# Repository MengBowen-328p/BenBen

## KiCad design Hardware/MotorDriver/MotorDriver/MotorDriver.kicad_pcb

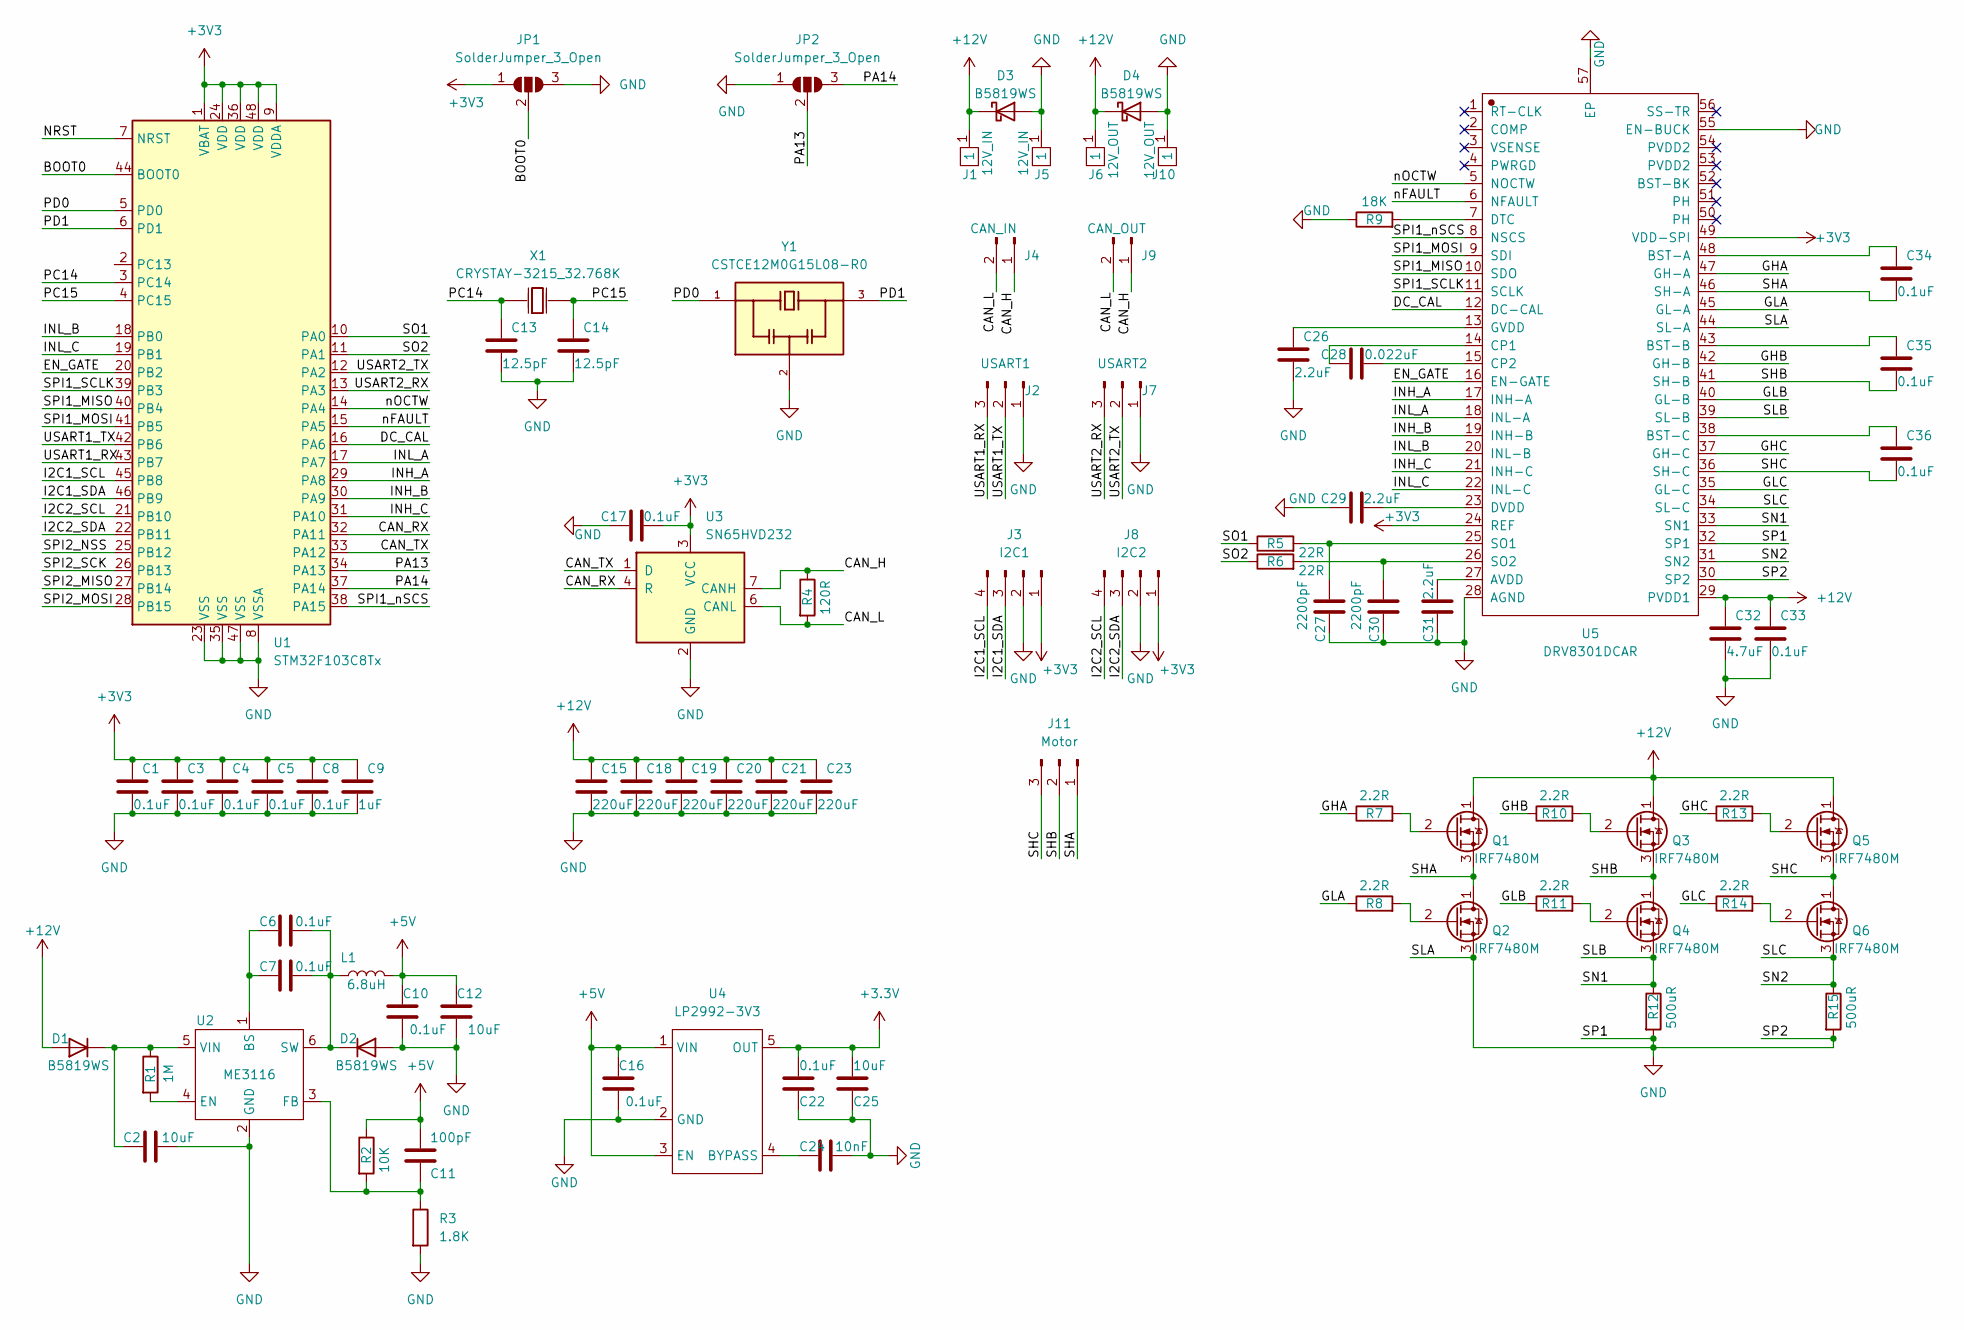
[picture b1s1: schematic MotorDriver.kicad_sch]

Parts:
C1, C3, C4, C5, C6, C7, C8, C10, C16, C17, C22, C33, C34, C35, C36: 0.1uF; C_0402_1005Metric
C2, C12, C25: 10uF; C_0402_1005Metric
C9: 1uF; C_0402_1005Metric
C11: 100pF; C_0402_1005Metric
C13, C14: 12.5pF; C_0402_1005Metric
C15, C18, C19, C20, C21, C23: 220uF; C_1206_3216Metric
C24: 10nF; C_0402_1005Metric
C26, C29, C31: 2.2uF; C_0402_1005Metric
C27, C30: 2200pF; C_0402_1005Metric
C28: 0.022uF; C_0402_1005Metric
C32: 4.7uF; C_0402_1005Metric
D1, D2, D3, D4: B5819WS; D_SOD-323
J1, J5: 12V_IN; PowerPad
J2: USART1; JST_ZE_SM03B-ZESS-TB_1x03-1MP_P1.50mm_Horizontal
J3: I2C1; JST_ZE_SM04B-ZESS-TB_1x04-1MP_P1.50mm_Horizontal
J4: CAN_IN; JST_ZE_SM02B-ZESS-TB_1x02-1MP_P1.50mm_Horizontal
J6, J10: 12V_OUT; PowerPad
J7: USART2; JST_ZE_SM03B-ZESS-TB_1x03-1MP_P1.50mm_Horizontal
J8: I2C2; JST_ZE_SM04B-ZESS-TB_1x04-1MP_P1.50mm_Horizontal
J9: CAN_OUT; JST_ZE_SM02B-ZESS-TB_1x02-1MP_P1.50mm_Horizontal
J11: Motor; MR30_SMD
JP1, JP2: SolderJumper_3_Open; SolderJumper-3_P1.3mm_Open_Pad1.0x1.5mm
L1: 6.8uH; L_0805_2012Metric
Q1, Q2, Q3, Q4, Q5, Q6: IRF7480M; DirectFET_ME
R1: 1M; R_0402_1005Metric
R2: 10K; R_0402_1005Metric
R3: 1.8K; R_0402_1005Metric
R4: 120R; R_0402_1005Metric
R5, R6: 22R; R_0402_1005Metric
R7, R8, R10, R11, R13, R14: 2.2R; R_0402_1005Metric
R9: 18K; R_0402_1005Metric
R12, R15: 500uR; R_2512_6332Metric
U1: STM32F103C8Tx; LQFP-48_7x7mm_P0.5mm
U2: ME3116; SOT-23-6
U3: SN65HVD232; SOIC-8_3.9x4.9mm_P1.27mm
U4: LP2992-3V3; SOT-23-5
U5: DRV8301DCAR; HTSSOP-56_L14.0-W6.0-P0.50-LS8.0-BL
X1: CRYSTAY-3215_32.768K; CRYSTAL-SMD_L3.2-W1.5-FC-135R32.7680KF-A3
Y1: CSTCE12M0G15L08-R0; OSC_CSTCE12M0G15L08-R0; PARTREV May 7, 2019

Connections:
+5V: C10.2, C11.1, C12.2, C16.2, L1.2, R2.1, U4.1 (VIN), U4.3 (EN)
+12V: C15.1, C18.1, C19.1, C20.1, C21.1, C23.1, C32.1, C33.1, D1.2 (A), D3.1 (K), D4.1 (K), J1.1, J6.1, Q1.1 (D), Q3.1 (D), Q5.1 (D), U5.29 (PVDD1)
/BOOT0: JP1.2 (C), U1.44 (BOOT0)
/CAN_H: J4.1, J9.1, R4.1, U3.7 (CANH)
/CAN_L: J4.2, J9.2, R4.2, U3.6 (CANL)
/CAN_RX: U1.32 (PA11), U3.4 (R)
/CAN_TX: U1.33 (PA12), U3.1 (D)
/DC_CAL: U1.16 (PA6), U5.12 (DC-CAL)
/EN_GATE: U1.20 (PB2), U5.16 (EN-GATE)
/GHA: R7.1, U5.47 (GH-A)
/GHB: R10.1, U5.42 (GH-B)
/GHC: R13.1, U5.37 (GH-C)
/GLA: R8.1, U5.45 (GL-A)
/GLB: R11.1, U5.40 (GL-B)
/GLC: R14.1, U5.35 (GL-C)
/I2C1_SCL: J3.4, U1.45 (PB8)
/I2C1_SDA: J3.3, U1.46 (PB9)
/I2C2_SCL: J8.4, U1.21 (PB10)
/I2C2_SDA: J8.3, U1.22 (PB11)
/INH_A: U1.29 (PA8), U5.17 (INH-A)
/INH_B: U1.30 (PA9), U5.19 (INH-B)
/INH_C: U1.31 (PA10), U5.21 (INH-C)
/INL_A: U1.17 (PA7), U5.18 (INL-A)
/INL_B: U1.18 (PB0), U5.20 (INL-B)
/INL_C: U1.19 (PB1), U5.22 (INL-C)
/NRST: U1.7 (NRST)
/PA13: JP2.2 (C), U1.34 (PA13)
/PA14: JP2.3 (B), U1.37 (PA14)
/PC14: C13.1, U1.3 (PC14), X1.1 (OSC1)
/PC15: C14.1, U1.4 (PC15), X1.2 (OSC2)
/PD0: U1.5 (PD0), Y1.1
/PD1: U1.6 (PD1), Y1.3
/SHA: C34.2, J11.1, Q1.3 (S), Q2.1 (D), U5.46 (SH-A)
/SHB: C35.2, J11.2, Q3.3 (S), Q4.1 (D), U5.41 (SH-B)
/SHC: C36.2, J11.3, Q5.3 (S), Q6.1 (D), U5.36 (SH-C)
/SLB: Q4.3 (S), R12.1, U5.33 (SN1), U5.39 (SL-B)
/SLC: Q6.3 (S), R15.1, U5.31 (SN2), U5.34 (SL-C)
/SO1: R5.1, U1.10 (PA0)
/SO2: R6.1, U1.11 (PA1)
/SPI1_MISO: U1.40 (PB4), U5.10 (SDO)
/SPI1_MOSI: U1.41 (PB5), U5.9 (SDI)
/SPI1_SCLK: U1.39 (PB3), U5.11 (SCLK)
/SPI1_nSCS: U1.38 (PA15), U5.8 (NSCS)
/SPI2_MISO: U1.27 (PB14)
/SPI2_MOSI: U1.28 (PB15)
/SPI2_NSS: U1.25 (PB12)
/SPI2_SCK: U1.26 (PB13)
/USART1_RX: J2.3, U1.43 (PB7)
/USART1_TX: J2.2, U1.42 (PB6)
/USART2_RX: J7.3, U1.13 (PA3)
/USART2_TX: J7.2, U1.12 (PA2)
/nFAULT: U1.15 (PA5), U5.6 (NFAULT)
/nOCTW: U1.14 (PA4), U5.5 (NOCTW)
GND: C1.2, C2.2, C3.2, C4.2, C5.2, C8.2, C9.2, C10.1, C12.1, C13.2, C14.2, C15.2, C16.1, C17.1, C18.2, C19.2, C20.2, C21.2, C22.2, C23.2, C24.1, C25.2, C26.2, C27.1, C29.1, C30.1, C31.1, C32.2, C33.2, D2.2 (A), D3.2 (A), D4.2 (A), J2.1, J3.2, J5.1, J7.1, J8.2, J10.1, JP1.3 (B), JP2.1 (A), Q2.3 (S), R3.2, R9.1, R12.2, R15.2, U1.8 (VSSA), U1.23 (VSS), U1.35 (VSS), U1.47 (VSS), U2.2 (GND), U3.2 (GND), U4.2 (GND), U5.28 (AGND), U5.30 (SP2), U5.32 (SP1), U5.44 (SL-A), U5.55 (EN-BUCK), U5.57 (EP), Y1.2
unnamed: C2.1, D1.1 (K), R1.1, U2.5 (VIN)
unnamed: C6.1, C7.1, D2.1 (K), L1.1, U2.6 (SW)
unnamed: C6.2, C7.2, U2.1 (BS)
unnamed: C11.2, R2.2, R3.1, U2.3 (FB)
unnamed: C24.2, U4.4 (BYPASS)
unnamed: C26.1, U5.13 (GVDD)
unnamed: C27.2, R5.2, U5.25 (SO1)
unnamed: C28.1, U5.14 (CP1)
unnamed: C28.2, U5.15 (CP2)
unnamed: C29.2, U5.23 (DVDD)
unnamed: C30.2, R6.2, U5.26 (SO2)
unnamed: C31.2, U5.27 (AVDD)
unnamed: C34.1, U5.48 (BST-A)
unnamed: C35.1, U5.43 (BST-B)
unnamed: C36.1, U5.38 (BST-C)
unnamed: Q1.2 (G), R7.2
unnamed: Q2.2 (G), R8.2
unnamed: Q3.2 (G), R10.2
unnamed: Q4.2 (G), R11.2
unnamed: Q5.2 (G), R13.2
unnamed: Q6.2 (G), R14.2
unnamed: R1.2, U2.4 (EN)
unnamed: R9.2, U5.7 (DTC)

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
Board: 4 copper layers, 82 parts (2 on the bottom side), 73 nets, no tracks yet.

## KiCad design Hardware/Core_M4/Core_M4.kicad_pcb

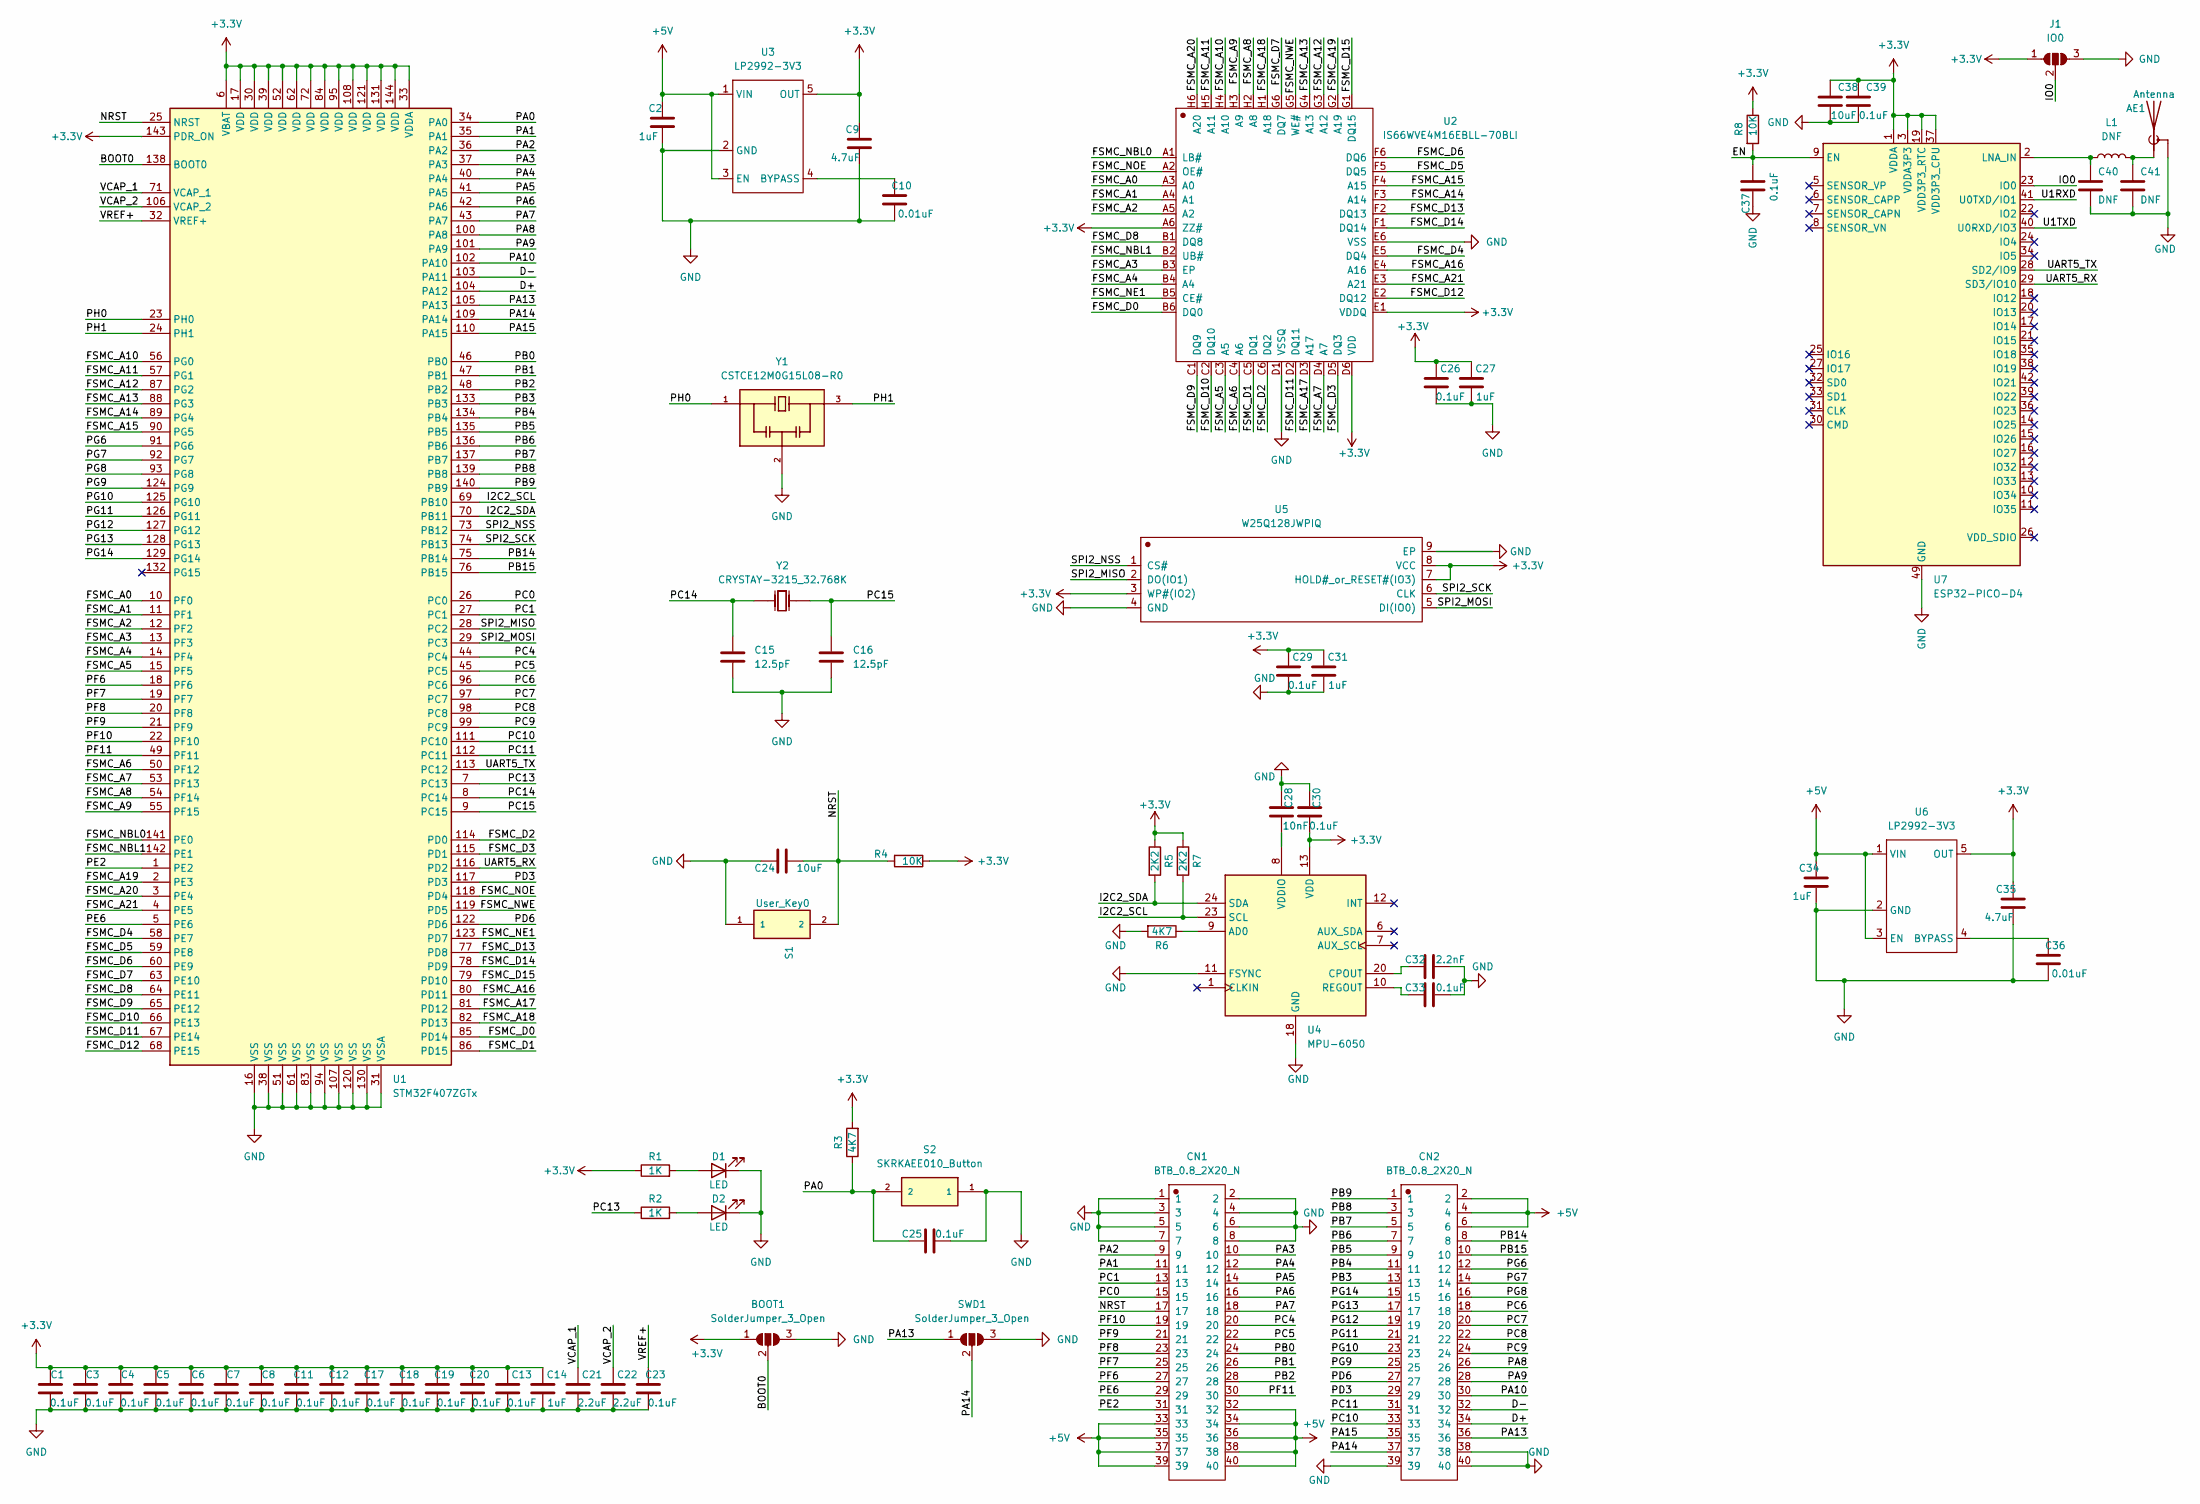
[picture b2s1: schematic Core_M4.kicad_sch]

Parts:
AE1: Antenna; Johanson_2450AT43F0100
BOOT1: SolderJumper_3_Open; SolderJumper-3_P1.3mm_Open_Pad1.0x1.5mm_NumberLabels
C1, C3, C4, C5, C6, C7, C8, C11, C12, C13, C17, C18, C19, C20, C23, C25, C26, C29, C30, C33, C37, C39: 0.1uF; C_0402_1005Metric
C2, C14, C27, C31, C34: 1uF; C_0402_1005Metric
C9, C35: 4.7uF; C_0402_1005Metric
C10, C36: 0.01uF; C_0402_1005Metric
C15, C16: 12.5pF; C_0402_1005Metric
C21, C22: 2.2uF; C_0402_1005Metric
C24, C38: 10uF; C_0402_1005Metric
C28: 10nF; C_0402_1005Metric
C32: 2.2nF; C_0402_1005Metric
C40, C41: DNF; C_0402_1005Metric
CN1, CN2: BTB_0.8_2X20_N; CONN-SMD_40P-P0.80_BTB_0.8_2X20_N
D1, D2: LED; LED_0402_1005Metric
J1: IO0; SolderJumper-3_P1.3mm_Open_RoundedPad1.0x1.5mm
L1: DNF; L_0402_1005Metric
R1, R2: 1K; R_0402_1005Metric
R3, R6: 4K7; R_0402_1005Metric
R4, R8: 10K; R_0402_1005Metric
R5, R7: 2K2; R_0402_1005Metric
S1: User_Key0; SKRK; Manufacturer_Part_Number SKRKAEE010
S2: SKRKAEE010_Button; SKRK; Manufacturer_Part_Number SKRKAEE010
SWD1: SolderJumper_3_Open; SolderJumper-3_P1.3mm_Open_Pad1.0x1.5mm_NumberLabels
U1: STM32F407ZGTx; LQFP-144_20x20mm_P0.5mm
U2: IS66WVE4M16EBLL-70BLI; TFBGA-48_L8.0-W6.0-R8-C6-P0.75-TL
U3, U6: LP2992-3V3; SOT-23-5
U4: MPU-6050; InvenSense_QFN-24_4x4mm_P0.5mm
U5: W25Q128JWPIQ; WSON-8_L6.0-W5.0-P1.27-BL-EP
U7: ESP32-PICO-D4; QFN-48-1EP_7x7mm_P0.5mm_EP5.3x5.3mm
Y1: CSTCE12M0G15L08-R0; OSC_CSTCE12M0G15L08-R0; PARTREV May 7, 2019
Y2: CRYSTAY-3215_32.768K; CRYSTAL-SMD_L3.2-W1.5-FC-135R32.7680KF-A3

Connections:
+3V3: BOOT1.1 (A), C1.1, C3.1, C4.1, C5.1, C6.1, C7.1, C8.1, C9.1, C11.1, C12.1, C13.1, C14.1, C17.1, C18.1, C19.1, C20.1, C26.1, C27.1, C29.1, C30.2, C31.1, C35.1, C38.1, C39.1, J1.1 (A), R1.1, R3.2, R4.1, R5.1, R7.1, R8.1, U1.6 (VBAT), U1.17 (VDD), U1.30 (VDD), U1.33 (VDDA), U1.39 (VDD), U1.52 (VDD), U1.62 (VDD), U1.72 (VDD), U1.84 (VDD), U1.95 (VDD), U1.108 (VDD), U1.121 (VDD), U1.131 (VDD), U1.143 (PDR_ON), U1.144 (VDD), U2.A6 (ZZ#), U2.D6 (VDD), U2.E1 (VDDQ), U3.5 (OUT), U4.13 (VDD), U5.3 (WP#(IO2)), U5.7 (HOLD#_or_RESET#(IO3)), U5.8 (VCC), U6.5 (OUT), U7.1 (VDDA), U7.3 (VDDA3P3), U7.4 (VDDA3P3), U7.19 (VDD3P3_RTC), U7.37 (VDD3P3_CPU), U7.43 (VDDA), U7.46 (VDDA); also elsewhere on the board
+5V: C2.1, C34.1, CN1.32, CN1.33, CN1.34, CN1.35, CN1.36, CN1.37, CN1.38, CN1.39, CN1.40, CN2.2, CN2.4, CN2.6, U3.1 (VIN), U3.3 (EN), U6.1 (VIN), U6.3 (EN)
/BOOT0: BOOT1.2 (C), U1.138 (BOOT0); also elsewhere on the board
/D+: CN2.34, U1.104 (PA12)
/D-: CN2.32, U1.103 (PA11)
/EN: C37.2, R8.2, U7.9 (EN)
/FSMC_A0: U1.10 (PF0), U2.A3 (A0)
/FSMC_A1: U1.11 (PF1), U2.A4 (A1)
/FSMC_A2: U1.12 (PF2), U2.A5 (A2)
/FSMC_A3: U1.13 (PF3), U2.B3 (EP)
/FSMC_A4: U1.14 (PF4), U2.B4 (A4)
/FSMC_A5: U1.15 (PF5), U2.C3 (A5)
/FSMC_A6: U1.50 (PF12), U2.C4 (A6)
/FSMC_A7: U1.53 (PF13), U2.D4 (A7)
/FSMC_A8: U1.54 (PF14), U2.H2 (A8)
/FSMC_A9: U1.55 (PF15), U2.H3 (A9)
/FSMC_A10: U1.56 (PG0), U2.H4 (A10)
/FSMC_A11: U1.57 (PG1), U2.H5 (A11)
/FSMC_A12: U1.87 (PG2), U2.G3 (A12)
/FSMC_A13: U1.88 (PG3), U2.G4 (A13)
/FSMC_A14: U1.89 (PG4), U2.F3 (A14)
/FSMC_A15: U1.90 (PG5), U2.F4 (A15)
/FSMC_A16: U1.80 (PD11), U2.E4 (A16)
/FSMC_A17: U1.81 (PD12), U2.D3 (A17)
/FSMC_A18: U1.82 (PD13), U2.H1 (A18)
/FSMC_A19: U1.2 (PE3), U2.G2 (A19)
/FSMC_A20: U1.3 (PE4), U2.H6 (A20)
/FSMC_A21: U1.4 (PE5), U2.E3 (A21)
/FSMC_D0: U1.85 (PD14), U2.B6 (DQ0)
/FSMC_D1: U1.86 (PD15), U2.C5 (DQ1)
/FSMC_D2: U1.114 (PD0), U2.C6 (DQ2)
/FSMC_D3: U1.115 (PD1), U2.D5 (DQ3)
/FSMC_D4: U1.58 (PE7), U2.E5 (DQ4)
/FSMC_D5: U1.59 (PE8), U2.F5 (DQ5)
/FSMC_D6: U1.60 (PE9), U2.F6 (DQ6)
/FSMC_D7: U1.63 (PE10), U2.G6 (DQ7)
/FSMC_D8: U1.64 (PE11), U2.B1 (DQ8)
/FSMC_D9: U1.65 (PE12), U2.C1 (DQ9)
/FSMC_D10: U1.66 (PE13), U2.C2 (DQ10)
/FSMC_D11: U1.67 (PE14), U2.D2 (DQ11)
/FSMC_D12: U1.68 (PE15), U2.E2 (DQ12)
/FSMC_D13: U1.77 (PD8), U2.F2 (DQ13)
/FSMC_D14: U1.78 (PD9), U2.F1 (DQ14)
/FSMC_D15: U1.79 (PD10), U2.G1 (DQ15)
/FSMC_NBL0: U1.141 (PE0), U2.A1 (LB#)
/FSMC_NBL1: U1.142 (PE1), U2.B2 (UB#)
/FSMC_NE1: U1.123 (PD7), U2.B5 (CE#)
/FSMC_NOE: U1.118 (PD4), U2.A2 (OE#)
/FSMC_NWE: U1.119 (PD5), U2.G5 (WE#)
/I2C2_SCL: R7.2, U1.69 (PB10), U4.23 (SCL)
/I2C2_SDA: R5.2, U1.70 (PB11), U4.24 (SDA)
/IO0: J1.2 (C), U7.23 (IO0)
/NRST: C24.1, CN1.17, R4.2, S1.2, U1.25 (NRST)
/PA0: C25.1, R3.1, S2.2, U1.34 (PA0)
/PA1: CN1.11, U1.35 (PA1)
/PA2: CN1.9, U1.36 (PA2)
/PA3: CN1.10, U1.37 (PA3)
/PA4: CN1.12, U1.40 (PA4)
/PA5: CN1.14, U1.41 (PA5)
/PA6: CN1.16, U1.42 (PA6)
/PA7: CN1.18, U1.43 (PA7)
/PA8: CN2.26, U1.100 (PA8)
/PA9: CN2.28, U1.101 (PA9)
/PA10: CN2.30, U1.102 (PA10)
/PA13: CN2.36, SWD1.1 (A), U1.105 (PA13); also elsewhere on the board
/PA14: CN2.37, SWD1.2 (C), U1.109 (PA14); also elsewhere on the board
/PA15: CN2.35, U1.110 (PA15)
/PB0: CN1.24, U1.46 (PB0)
/PB1: CN1.26, U1.47 (PB1)
/PB2: CN1.28, U1.48 (PB2)
/PB3: CN2.13, U1.133 (PB3)
/PB4: CN2.11, U1.134 (PB4)
/PB5: CN2.9, U1.135 (PB5)
/PB6: CN2.7, U1.136 (PB6)
/PB7: CN2.5, U1.137 (PB7)
/PB8: CN2.3, U1.139 (PB8)
/PB9: CN2.1, U1.140 (PB9)
/PB14: CN2.8, U1.75 (PB14)
/PB15: CN2.10, U1.76 (PB15)
/PC0: CN1.15, U1.26 (PC0)
/PC1: CN1.13, U1.27 (PC1)
/PC4: CN1.20, U1.44 (PC4)
/PC5: CN1.22, U1.45 (PC5)
/PC6: CN2.18, U1.96 (PC6)
/PC7: CN2.20, U1.97 (PC7)
/PC8: CN2.22, U1.98 (PC8)
/PC9: CN2.24, U1.99 (PC9)
/PC10: CN2.33, U1.111 (PC10)
/PC11: CN2.31, U1.112 (PC11)
/PC13: R2.1, U1.7 (PC13)
/PC14: C15.1, U1.8 (PC14), Y2.1 (OSC1)
/PC15: C16.1, U1.9 (PC15), Y2.2 (OSC2)
/PD3: CN2.29, U1.117 (PD3)
/PD6: CN2.27, U1.122 (PD6)
/PE2: CN1.31, U1.1 (PE2)
/PE6: CN1.29, U1.5 (PE6)
/PF6: CN1.27, U1.18 (PF6)
/PF7: CN1.25, U1.19 (PF7)
/PF8: CN1.23, U1.20 (PF8)
/PF9: CN1.21, U1.21 (PF9)
/PF10: CN1.19, U1.22 (PF10)
/PF11: CN1.30, U1.49 (PF11)
/PG6: CN2.12, U1.91 (PG6)
/PG7: CN2.14, U1.92 (PG7)
/PG8: CN2.16, U1.93 (PG8)
/PG9: CN2.25, U1.124 (PG9)
/PG10: CN2.23, U1.125 (PG10)
/PG11: CN2.21, U1.126 (PG11)
/PG12: CN2.19, U1.127 (PG12)
/PG13: CN2.17, U1.128 (PG13)
/PG14: CN2.15, U1.129 (PG14)
/PH0: U1.23 (PH0), Y1.1
/PH1: U1.24 (PH1), Y1.3
/SPI2_MISO: U1.28 (PC2), U5.2 (DO(IO1))
/SPI2_MOSI: U1.29 (PC3), U5.5 (DI(IO0))
/SPI2_NSS: U1.73 (PB12), U5.1 (CS#)
/SPI2_SCK: U1.74 (PB13), U5.6 (CLK)
/U1RXD: U7.41 (U0TXD/IO1)
/U1TXD: U7.40 (U0RXD/IO3)
/UART5_RX: U1.116 (PD2), U7.29 (SD3/IO10)
/UART5_TX: U1.113 (PC12), U7.28 (SD2/IO9)
/VCAP_1: C21.1, U1.71 (VCAP_1)
/VCAP_2: C22.1, U1.106 (VCAP_2)
/VREF+: C23.1, U1.32 (VREF+)
GND: AE1.2 (Shield), BOOT1.3 (B), C1.2, C2.2, C3.2, C4.2, C5.2, C6.2, C7.2, C8.2, C9.2, C10.2, C11.2, C12.2, C13.2, C14.2, C15.2, C16.2, C17.2, C18.2, C19.2, C20.2, C21.2, C22.2, C23.2, C24.2, C25.2, C26.2, C27.2, C28.1, C29.2, C30.1, C31.2, C32.2, C33.2, C34.2, C35.2, C36.2, C37.1, C38.2, C39.2, C40.2, C41.2, CN1.1, CN1.2, CN1.3, CN1.4, CN1.5, CN1.6, CN1.7, CN1.8, CN2.38, CN2.39, CN2.40, D1.1 (K), D2.1 (K), J1.3 (B), R6.2, S1.1, S2.1, SWD1.3 (B), U1.16 (VSS), U1.31 (VSSA), U1.38 (VSS), U1.51 (VSS), U1.61 (VSS), U1.83 (VSS), U1.94 (VSS), U1.107 (VSS), U1.120 (VSS), U1.130 (VSS), U2.D1 (VSSQ), U2.E6 (VSS), U3.2 (GND), U4.11 (FSYNC), U4.18 (GND), U5.4 (GND), U5.9 (EP), U6.2 (GND), U7.49 (GND), Y1.2; also elsewhere on the board
unnamed: AE1.1 (A), C41.1, L1.2
unnamed: C10.1, U3.4 (BYPASS)
unnamed: C28.2, U4.8 (VDDIO)
unnamed: C32.1, U4.20 (CPOUT)
unnamed: C33.1, U4.10 (REGOUT)
unnamed: C36.1, U6.4 (BYPASS)
unnamed: C40.1, L1.1, U7.2 (LNA_IN)
unnamed: D1.2 (A), R1.2
unnamed: D2.2 (A), R2.2
unnamed: R6.1, U4.9 (AD0)

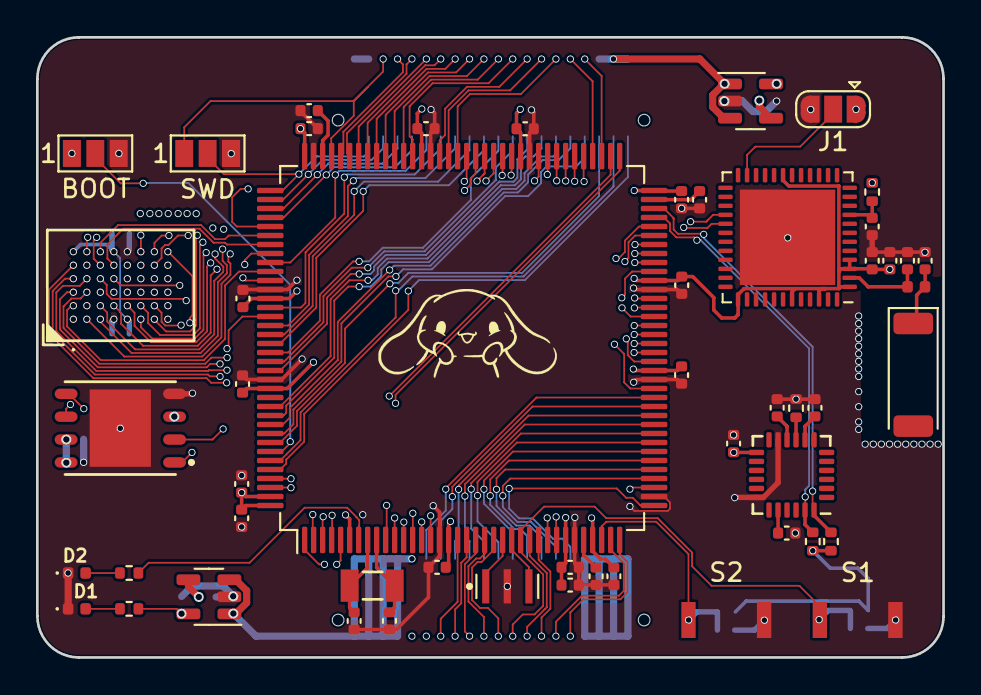
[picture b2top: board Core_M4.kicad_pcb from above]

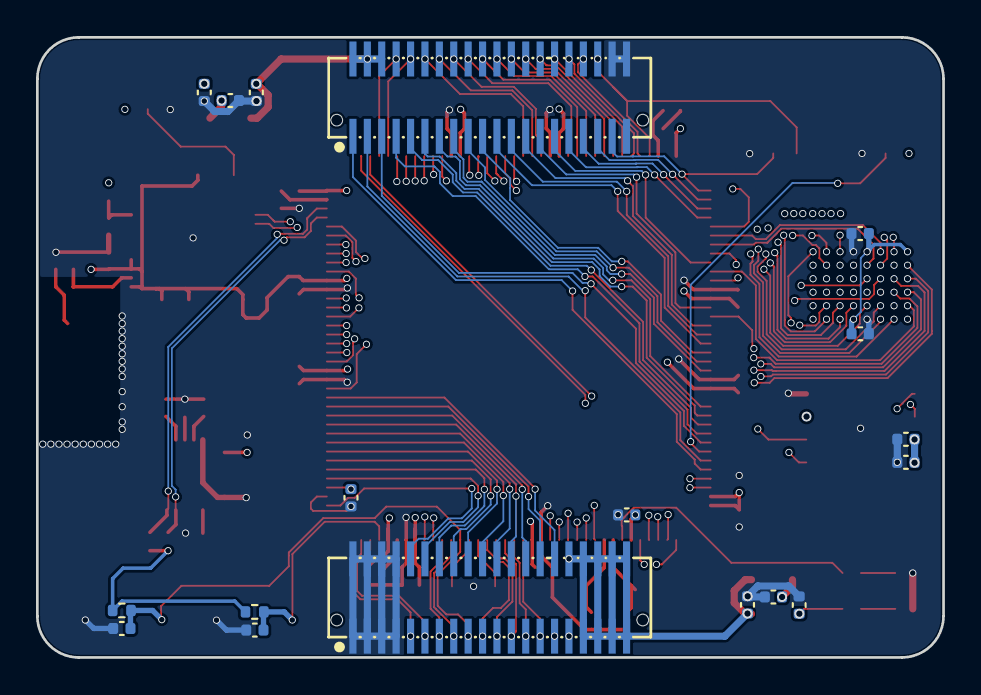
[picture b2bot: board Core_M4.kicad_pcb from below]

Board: 6 copper layers, 50.3 x 34.5 mm, 70 parts (18 on the bottom side), 133 nets.

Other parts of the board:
BOOT: SolderJumper_3_Open; SolderJumper-3_P1.3mm_Open_Pad1.0x1.5mm_NumberLabels
C11#2: 0.1uF; C_0402_1005Metric
SWD: SolderJumper_3_Open; SolderJumper-3_P1.3mm_Open_Pad1.0x1.5mm_NumberLabels

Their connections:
+3V3: BOOT.1 (A), C11#2.1; also elsewhere on the board
/BOOT0: BOOT.2 (C); also elsewhere on the board
/PA13: SWD.1 (A); also elsewhere on the board
/PA14: SWD.2 (C); also elsewhere on the board
GND: BOOT.3 (B), C11#2.2, SWD.3 (B); also elsewhere on the board

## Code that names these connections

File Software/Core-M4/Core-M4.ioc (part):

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Mcu.Name=STM32F407Z(E-G)Tx
Mcu.Package=LQFP144
Mcu.UserName=STM32F407ZGTx
PA11.Mode=Device_Only
PA11.Signal=USB_OTG_FS_DM
PA12.Mode=Device_Only
PA12.Signal=USB_OTG_FS_DP
PA13.Mode=Serial_Wire
PA13.Signal=SYS_JTMS-SWDIO
PA14.Mode=Serial_Wire
PA14.Signal=SYS_JTCK-SWCLK
PB10.Mode=I2C
PB10.Signal=I2C2_SCL
PB11.Mode=I2C
PB11.Signal=I2C2_SDA
PB12.Mode=NSS_Signal_Hard_Output
PB12.Signal=SPI2_NSS
PB13.Mode=Full_Duplex_Master
PB13.Signal=SPI2_SCK
PB8.Mode=CAN_Activate
PB8.Signal=CAN1_RX
PB9.Mode=CAN_Activate
PB9.Signal=CAN1_TX
PC12.Mode=Asynchronous
PC12.Signal=UART5_TX
PC13-ANTI_TAMP.GPIOParameters=GPIO_Label
PC13-ANTI_TAMP.GPIO_Label=User_LED
PC13-ANTI_TAMP.Signal=GPIO_Output
PC14-OSC32_IN.Mode=LSE-External-Oscillator
PC14-OSC32_IN.Signal=RCC_OSC32_IN
PC15-OSC32_OUT.Mode=LSE-External-Oscillator
PC15-OSC32_OUT.Signal=RCC_OSC32_OUT
PC2.Mode=Full_Duplex_Master
PC2.Signal=SPI2_MISO
PC3.Mode=Full_Duplex_Master
PC3.Signal=SPI2_MOSI
PD0.Signal=FSMC_D2_DA2
PD1.Signal=FSMC_D3_DA3
PD10.Signal=FSMC_D15_DA15
PD11.Signal=FSMC_A16_CLE
PD12.Signal=FSMC_A17_ALE
PD13.Signal=FSMC_A18
PD14.Signal=FSMC_D0_DA0
PD15.Signal=FSMC_D1_DA1
PD2.Mode=Asynchronous
PD2.Signal=UART5_RX
PD4.Signal=FSMC_NOE
PD5.Signal=FSMC_NWE
PD7.Mode=NorPsramChipSelect1_1
PD7.Signal=FSMC_NE1
PD8.Signal=FSMC_D13_DA13
PD9.Signal=FSMC_D14_DA14
PE0.Signal=FSMC_NBL0
PE1.Signal=FSMC_NBL1
PE10.Signal=FSMC_D7_DA7
PE11.Signal=FSMC_D8_DA8
PE12.Signal=FSMC_D9_DA9
PE13.Signal=FSMC_D10_DA10
PE14.Signal=FSMC_D11_DA11
PE15.Signal=FSMC_D12_DA12
PE3.Signal=FSMC_A19
PE4.Signal=FSMC_A20
PE5.Signal=FSMC_A21
PE7.Signal=FSMC_D4_DA4
PE8.Signal=FSMC_D5_DA5
PE9.Signal=FSMC_D6_DA6
PF0.Signal=FSMC_A0
PF1.Signal=FSMC_A1
PF12.Signal=FSMC_A6
PF13.Signal=FSMC_A7
PF14.Signal=FSMC_A8
PF15.Signal=FSMC_A9
PF2.Signal=FSMC_A2
PF3.Signal=FSMC_A3
PF4.Signal=FSMC_A4
PF5.Signal=FSMC_A5
PG0.Signal=FSMC_A10
PG1.Signal=FSMC_A11
PG2.Signal=FSMC_A12
PG3.Signal=FSMC_A13
PG4.Signal=FSMC_A14
PG5.Signal=FSMC_A15
PH0-OSC_IN.Mode=HSE-External-Oscillator
PH0-OSC_IN.Signal=RCC_OSC_IN
PH1-OSC_OUT.Mode=HSE-External-Oscillator
PH1-OSC_OUT.Signal=RCC_OSC_OUT
RCC.HSE_VALUE=25000000
RCC.SYSCLKFreq_VALUE=168000000
RCC.SYSCLKSource=RCC_SYSCLKSOURCE_PLLCLK
board=custom

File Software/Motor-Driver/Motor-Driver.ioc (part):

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Mcu.Name=STM32F103C(8-B)Tx
Mcu.Package=LQFP48
Mcu.UserName=STM32F103C8Tx
PA0-WKUP.Signal=ADCx_IN0
PA1.Signal=ADCx_IN1
PA10.Signal=S_TIM1_CH3
PA11.Mode=CAN_Activate
PA11.Signal=CAN_RX
PA12.Mode=CAN_Activate
PA12.Signal=CAN_TX
PA13.Mode=Serial_Wire
PA13.Signal=SYS_JTMS-SWDIO
PA14.Mode=Serial_Wire
PA14.Signal=SYS_JTCK-SWCLK
PA15.Mode=NSS_Signal_Hard_Output
PA15.Signal=SPI1_NSS
PA2.Mode=Asynchronous
PA2.Signal=USART2_TX
PA3.Mode=Asynchronous
PA3.Signal=USART2_RX
PA4.GPIOParameters=GPIO_Label
PA4.GPIO_Label=nOCTW
PA4.Signal=GPIO_Output
PA5.GPIOParameters=GPIO_Label
PA5.GPIO_Label=nFAULT
PA5.Signal=GPIO_Output
PA6.GPIOParameters=GPIO_Label
PA6.GPIO_Label=DC_CAL
PA6.Signal=GPIO_Output
PA7.Mode=PWM Generation1 CH1 CH1N
PA7.Signal=TIM1_CH1N
PA8.Signal=S_TIM1_CH1
PA9.Signal=S_TIM1_CH2
PB0.Mode=PWM Generation2 CH2 CH2N
PB0.Signal=TIM1_CH2N
PB1.Mode=PWM Generation3 CH3 CH3N
PB1.Signal=TIM1_CH3N
PB10.Mode=I2C
PB10.Signal=I2C2_SCL
PB11.Mode=I2C
PB11.Signal=I2C2_SDA
PB12.Mode=NSS_Signal_Hard_Output
PB12.Signal=SPI2_NSS
PB13.Mode=Full_Duplex_Master
PB13.Signal=SPI2_SCK
PB14.Mode=Full_Duplex_Master
PB14.Signal=SPI2_MISO
PB15.Mode=Full_Duplex_Master
PB15.Signal=SPI2_MOSI
PB2.GPIOParameters=GPIO_Label
PB2.GPIO_Label=EN_GATE
PB2.Signal=GPIO_Output
PB3.Mode=Full_Duplex_Master
PB3.Signal=SPI1_SCK
PB4.Mode=Full_Duplex_Master
PB4.Signal=SPI1_MISO
PB5.Mode=Full_Duplex_Master
PB5.Signal=SPI1_MOSI
PB6.Mode=Asynchronous
PB6.Signal=USART1_TX
PB7.Mode=Asynchronous
PB7.Signal=USART1_RX
PB8.Mode=I2C
PB8.Signal=I2C1_SCL
PB9.Mode=I2C
PB9.Signal=I2C1_SDA
PC13-TAMPER-RTC.GPIOParameters=GPIO_Label
PC13-TAMPER-RTC.GPIO_Label=LED
PC13-TAMPER-RTC.Signal=GPIO_Output
PC14-OSC32_IN.Mode=LSE-External-Oscillator
PC14-OSC32_IN.Signal=RCC_OSC32_IN
PC15-OSC32_OUT.Mode=LSE-External-Oscillator
PC15-OSC32_OUT.Signal=RCC_OSC32_OUT
PD0-OSC_IN.Mode=HSE-External-Oscillator
PD0-OSC_IN.Signal=RCC_OSC_IN
PD1-OSC_OUT.Mode=HSE-External-Oscillator
PD1-OSC_OUT.Signal=RCC_OSC_OUT
RCC.HSEDivPLL=RCC_HSE_PREDIV_DIV2
RCC.HSE_VALUE=16000000
RCC.SYSCLKFreq_VALUE=72000000
RCC.SYSCLKSource=RCC_SYSCLKSOURCE_PLLCLK
board=custom

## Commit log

2023-02-01 Init Repo
